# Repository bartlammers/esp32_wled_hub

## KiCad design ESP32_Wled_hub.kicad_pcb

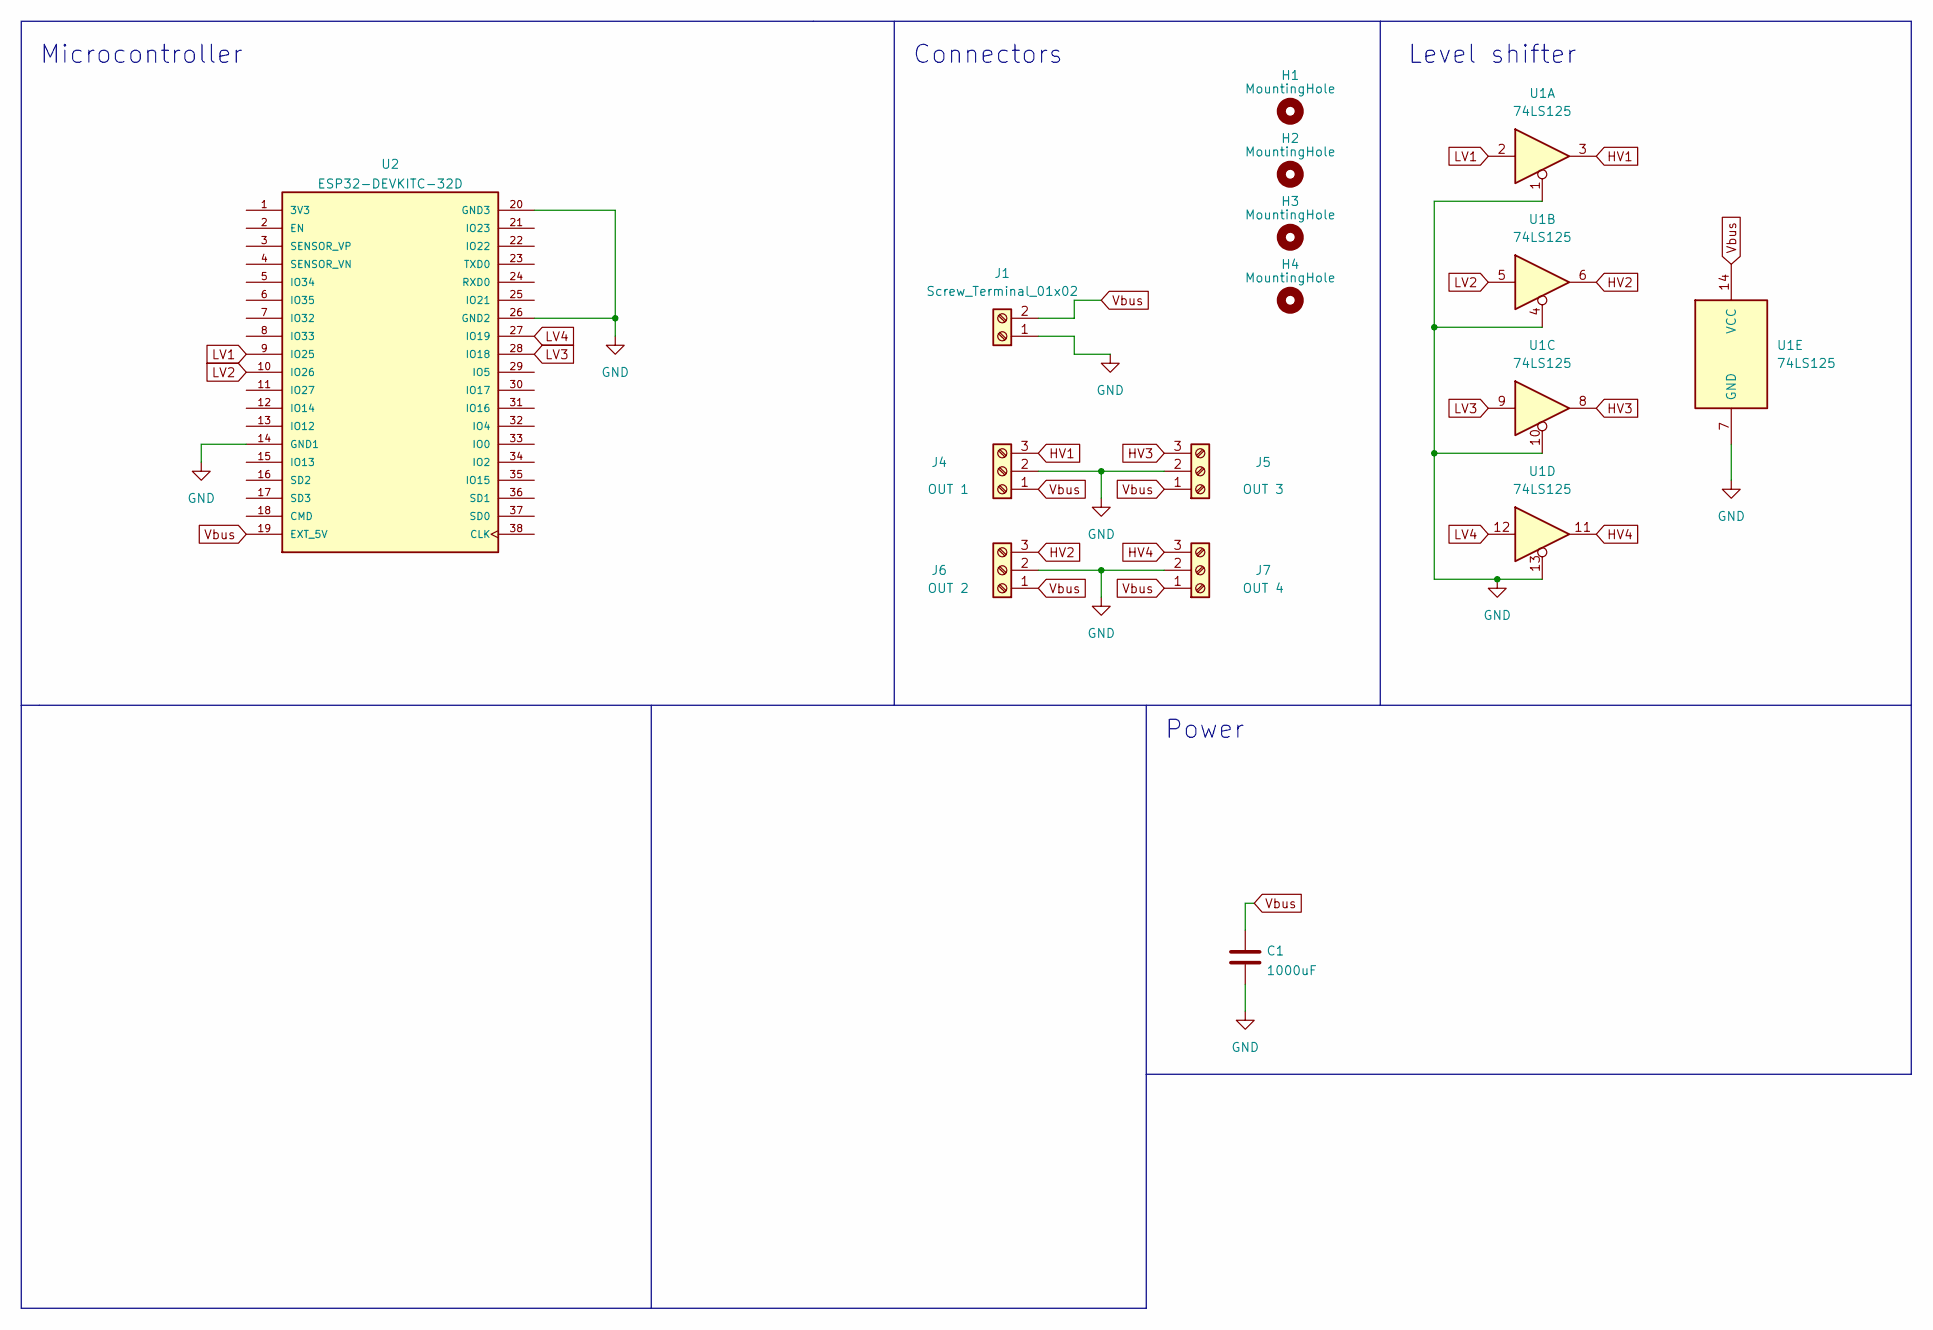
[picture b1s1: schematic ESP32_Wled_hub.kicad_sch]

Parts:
C1: 1000uF; C_Radial_D10.0mm_H16.0mm_P5.00mm
H1, H2, H3, H4: MountingHole; MountingHole_3.2mm_M3_Pad_Via
J1: Screw_Terminal_01x02; TerminalBlock_Phoenix_MKDS-1,5-2-5.08_1x02_P5.08mm_Horizont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
J4: OUT 1; TerminalBlock_Phoenix_MKDS-1,5-3-5.08_1x03_P5.08mm_Horizont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
J5: OUT 3; TerminalBlock_Phoenix_MKDS-1,5-3-5.08_1x03_P5.08mm_Horizont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
J6: OUT 2; TerminalBlock_Phoenix_MKDS-1,5-3-5.08_1x03_P5.08mm_Horizont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
J7: OUT 4; TerminalBlock_Phoenix_MKDS-1,5-3-5.08_1x03_P5.08mm_Horizont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
U1: 74LS125; SOIC-14-DIP-14-combo
U2: ESP32-DEVKITC-32D; MODULE_ESP32-DEVKITC-32D; PARTREV 4

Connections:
GND: C1.2, J1.1, J4.2, J5.2, J6.2, J7.2, U1.1, U1.4, U1.7 (GND), U1.10, U1.13, U2.14 (GND1), U2.20 (GND3), U2.26 (GND2)
HV1: J4.3, U1.3
HV2: J6.3, U1.6
HV3: J5.3, U1.8
HV4: J7.3, U1.11
LV1: U1.2, U2.9 (IO25)
LV2: U1.5, U2.10 (IO26)
LV3: U1.9, U2.28 (IO18)
LV4: U1.12, U2.27 (IO19)
Vbus: C1.1, J1.2, J4.1, J5.1, J6.1, J7.1, U1.14 (VCC), U2.19 (EXT_5V)

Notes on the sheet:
Microcontroller
Power
Connectors
Level shifter

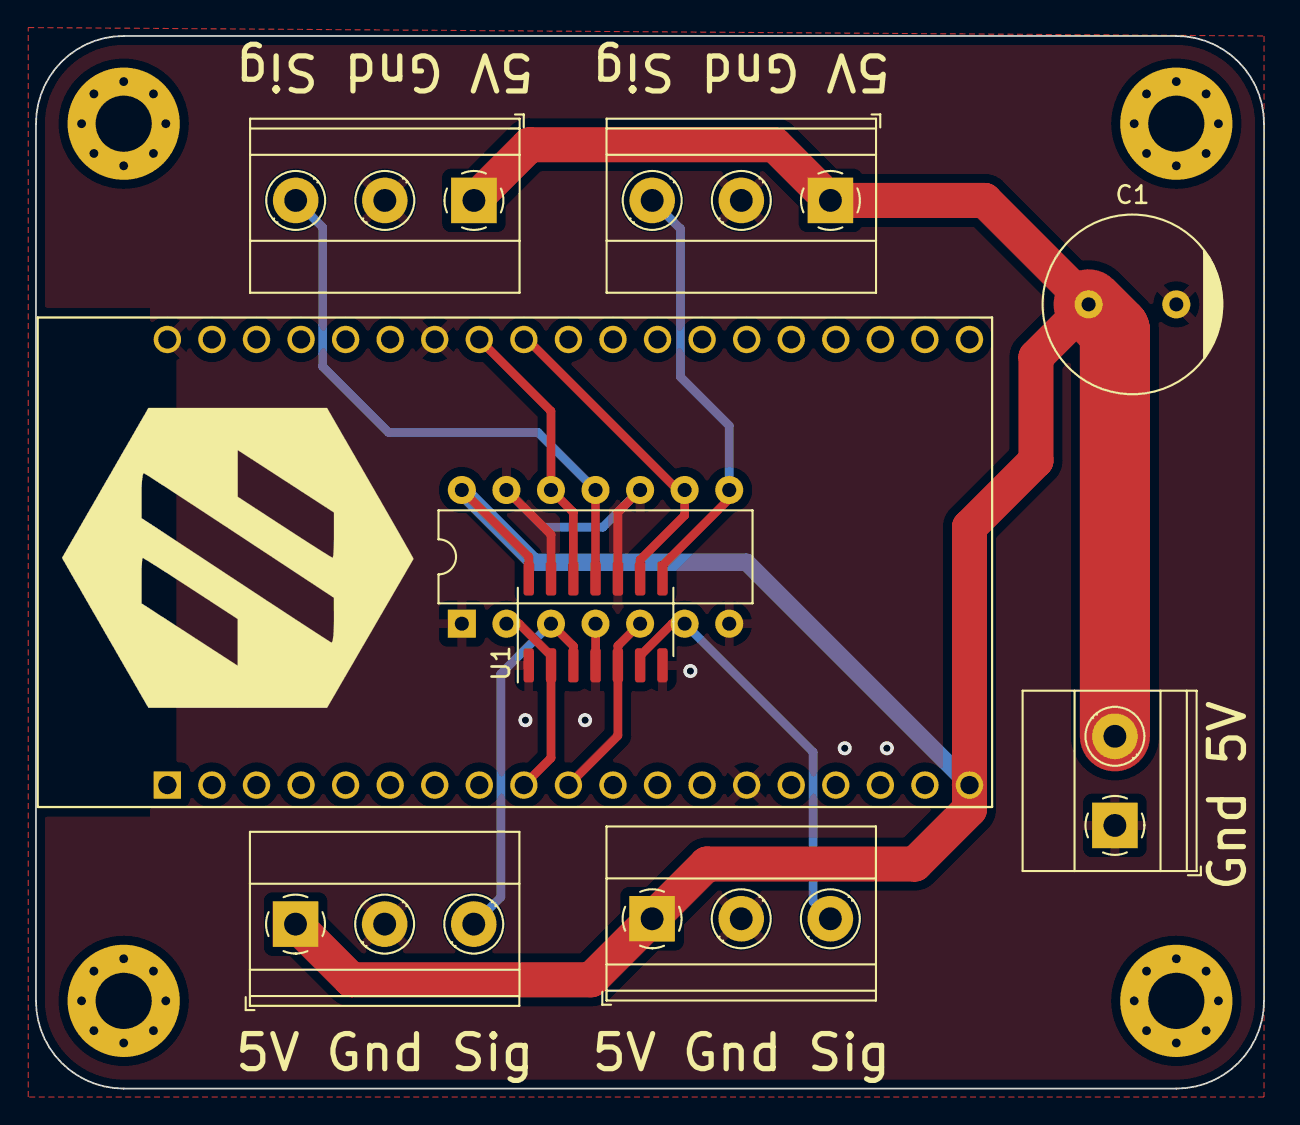
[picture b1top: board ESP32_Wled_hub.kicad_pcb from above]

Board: 2 copper layers, 70.0 x 60.0 mm, 12 parts (0 on the bottom side), 10 nets.

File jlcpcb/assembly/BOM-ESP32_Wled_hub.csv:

Comment,Designator,Footprint,LCSC
74LS125,U1,SOIC-14-DIP-14-combo,C7734
1000uF,C1,C_Radial_D10.0mm_H16.0mm_P5.00mm,
MountingHole,H4,MountingHole_3.2mm_M3_Pad_Via,
ESP32-DEVKITC-32D,U2,MODULE_ESP32-DEVKITC-32D,
MountingHole,H3,MountingHole_3.2mm_M3_Pad_Via,
OUT 1,J4,"TerminalBlock_Phoenix_MKDS-1,5-3-5.08_1x03_P5.08mm_Horizontal",
MountingHole,H1,MountingHole_3.2mm_M3_Pad_Via,
MountingHole,H2,MountingHole_3.2mm_M3_Pad_Via,
Screw_Terminal_01x02,J1,"TerminalBlock_Phoenix_MKDS-1,5-2-5.08_1x02_P5.08mm_Horizontal",
OUT 3,J5,"TerminalBlock_Phoenix_MKDS-1,5-3-5.08_1x03_P5.08mm_Horizontal",
OUT 2,J6,"TerminalBlock_Phoenix_MKDS-1,5-3-5.08_1x03_P5.08mm_Horizontal",
OUT 4,J7,"TerminalBlock_Phoenix_MKDS-1,5-3-5.08_1x03_P5.08mm_Horizontal",

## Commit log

2022-10-16 Cleanop old assembly files
